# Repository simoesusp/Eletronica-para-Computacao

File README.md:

# Eletronica-para-Computacao
Material Usado na disciplina de Eletrônica para Computação

Disciplina: SSC0180 - Eletrônica para Computação

Apresentação da Disciplina

Professor: Eduardo do Valle Simões
Email: Simoes at ICMC.USP.BR
Departamento de Sistemas de Computação – ICMC - USP
Grupo de Sistemas Embarcados e Evolutivos
Laboratório de Computação Reconfigurável

Créditos Aula: 	2
Créditos Trabalho: 	2
Tipo: 	Semestral

# Projeto Alunos 2019

- TODOS OS ALUNOS PRECISAM APRESENTAR O TRABALHO PESSOALMENTE!! Incluir no seu GIT: Software; Circuito com TODAS as conexoes com o Arduino; Fotos do circuito TOP VIEW; E um video mostrando o Projeto funcionando e explicando como construiu (Upa no Youtube e poe um link no teu Github). Dai' Forca a pagina da disciplina no teu git, edita o READ.ME e Comita. Depois faz um Pull Request No git original. Veja o video:

- Disco-Sound-Beat-Led-RGB (Lucas Gabriel, Mateus Penteado, Daniel Suzumura, Frederico Bulhoes)
https://github.com/LucasGab/Led-Controller
- Sistema de desbloqueio por senha (Fernando Lincoln, Victor Kendi, Leonardo Gabriel)
https://github.com/lincolncpp/senha-controle-remoto
- [Automação Residencial (Gabriel Souza, Rafael Tavares)] (https://github.com/gsasouza/house-automation)
https://github.com/gsasouza/house-automation
- Jogo da Velha (Thiago Sena, Victor Oliveira)
https://github.com/Thiago-SDQ/jogo_da_velha
- Arduino Genius Game (Dennis Green, Pedro Cisdeli, Pedro Lourenço):
https://github.com/Haltz01/Arduino_Genius
- Automação via Bot do Telegram (Gustavo Bartholomeu Trad Souza)
https://github.com/gustavobartho/Automacao_Residencial_Telegram_Bot
- 2D Penter - Impressora 2d para plotar gráficos (Breno Cunha Queiroz, Dikson Ferreira)
https://github.com/Brenocq/2DPenter
- Bomberman (André Santana, Gabriel Ferracioli, Kevin Naoto)
https://github.com/AndreSFND/Bomberman-Arduino
- Arduino controlado por Node.js (Leonardo Antonetti, Diogo Emídio, Jorge Augusto Salgado)
https://github.com/l-a-motta/arduino-node
- Fechadura Eletrica via WebServer (Joao Pedro Berno Zanutto)
https://github.com/zanuttin/Fechadura-WebServer
- Jogo de pong (Ana Clara Amorim, Kaio Tadeu Rodrigues)
https://github.com/AnaClaraAmorim/eletronica-para-computacao
- Sensor de temperatura (Gabriel Nicolau, Daniel Froes, Guilherme, Mateus Bragança)
https://github.com/7Nic/Sensor-de-temperatura
- Robô Omnidirecional (Lucas Romera, Maria Eduarda Kawakami, Otto Fernandes)
https://github.com/ottusp/Eletronica_Arduino
- Medidor de Temperatura e Umidade (César Guibo, Leonardo Rebelo, Ricardo Nascimento)
https://github.com/Rebelo/medidor_temp_umidade
- Xiloino: um instrumento musical (Paulo José, Jonathan Sanchez, Augusto de Elet)
https://gitlab.com/ImperfectFractal/xiloino
-Leitor de Morse por luz(Anderson Cardoso, Bruna Garcia, Hellen Rosa e Mateus de Souza)
https://github.com/OhMySt4rs/LeitordeMorse
- Exibição de mensagem em matriz de leds 8x8 (Marcus Vinícius Medeiros Pará, Luca Machado Bottino)
https://github.com/MarcusMedeiros99/max7219
- Simon42-Game (Bruna Magrini, Gustavo Akira, Marlon Martins, Wellington Amaral)
https://github.com/mjmartins11/projectsimon42
- Tradutor de Codigo Morse (Luis Otavio M. Ferreira, Leonardo F. Pinheiro, Luca M. Alexander, Maria Fernanda L. de Mello)
https://github.com/LuisOtavioMF/SCC0117-Trabalho2
- Rolador de Dados, com Seleção de dados (Guilherme Hiromoto, João Victor de Araujo Lima, Murilo Franchi Paulo Matana da Rocha, Vinicius Shimizu)
https://github.com/mrlFranchi/DiceRoller
- Genius Game With Sensor (Gabriel Rossati, Nathan Rodrigues e Yure Pablo):
https://github.com/yp1plus/geniusWithSensor_game
- Piano Hero (Bruno Fernandes Moreira, Francisco Pedrosa, Savio Duarte Fontes e Thales Willian Dalvi da Silva)
https:https://github.com/FranPedrosa/PianoHero<br/>
- Arduino Robot Car (Luca Batista Barbosa e Mylena Vieira Pim)
https://github.com/mylenapim/Arduino-Robot-Car
- Tradutor para Código Morse(Daniel Vieira, Vinícius Kuhlmann, Luis Rodrigues)
https://github.com/Idalen/Arduino_Morse_Translator
- Termômetro Digital (Eduardo Souza Rocha, Fabio Dias da Cunha)<br/>
https://github.com/Edwolt/Termometro-Arduino/
- Detector de Porta Aberta (Fernando Cincinato, Olavo Morais)
https://github.com/FernandoCincinato/Detector-de-porta-aberta-Arduino
- Arduino Pong Game (Diany Pressato Larissa Freire Luana Terra do Couto Matheus Araujo Tyago Teoi)
https://github.com/M-A-rs/Arduino-Pong-Game
- Sistema de monitoramento de umidade do solo (André Vieira, Leandro Satoshi)
https://github.com/LSatoshi/Soil_Moisture_Monitoring
- Dado-inator(Bernardo Andrade,Filipe Oliveira,Victor Russo,Yasmin Araújo)
https://github.com/vrrusso/dado-inator
- Labirinto Transdimensional em primeira pessoa (Dalton Sato, Marcus Martins, Vinícius de Araújo, Vitor Amim)
https://github.com/marcuscastelo/arduino-transdimentional-maze
- Piano de Bananas (Jose Daniel, Isadora Siebert, Erick Barcelos, Pablo Oliviera)
https://github.com/pabloolvr/Piano-de-Bananas
- Osciloscópio USB (Henrique Libutti, Matheus Borella, Natan Cerdeira)
https://github.com/natanbc/stm32_usb_scope
- Medidor de Pulso (Caio Marcos Chaves Viana; Lucas Carvalho Machado; Lucas Yuiti Oda Yamamoto; Gabriel de Oliveira Guedes Nogueira; Victor Gomes de Carvalho)
https://github.com/Talendar/arduino_pulse_monitor/blob/master/README.md
- Fonte da bancada (André Niero Setti)
https://github.com/Setti7/eletronica

# Video-aulas:

Screan Captured: https://www.youtube.com/watch?v=qb6fcfDH5Qk&t=2s

Screan Captured: https://www.youtube.com/watch?v=vQig6pRj4C4

Aula Tutorial EAGLE Parte 1: https://www.youtube.com/watch?v=jCn-QlsnRMU

Aula Tutorial EAGLE Parte 2: https://www.youtube.com/watch?v=TP7zXqjaEfo

# Não Faça em Casa

 - https://www.youtube.com/watch?v=slhocFSAoQE
 - https://www.youtube.com/watch?v=jBwodg8sfdU
 - https://www.youtube.com/watch?v=jUE1IHN6OI8
 - https://www.youtube.com/watch?v=yCwmYfkTInY

# Circuitos:

Porta NOT (nMOS e CMOS) http://tinyurl.com/y5shkxya

Cadeia NOT ERRADA (NPN)! http://tinyurl.com/y2mxmgwj

Cadeia NOT ERRADA!(nMOS) http://tinyurl.com/y6le5sgn

Fonte1 (Trafo-diodos-capacitor-led) http://tinyurl.com/y5793zjk

# Objetivos:

Familiarizar os alunos com o funcionamento eletrônico das portas e lógicas com conceitos relacionados a dispositivos eletrônicos.

Programa Resumido
Conceitos básicos de circuitos eletrônicos; caracterização dos componentes básicos: resistores, capacitores, diodos e transistores; projeto de circuitos eletrônicos com componentes básicos; projeto de funções lógicas com transistores: portas lógicas digitais; simulação de sinais elétricos em circuitos eletrônicos, efeitos transitórios na propagação de sinais elétricos em circuitos de lógica digital; projetos de fontes de tensão de corrente contínua.

Programa
Conceitos básicos de circuitos eletrônicos, com ênfase na utilização de componentes eletrônicos básicos, tais como resistores, capacitores, diodos e transistores, no projeto de circuitos e portas lógicas digitais. Uso de simuladores de circuitos elétricos para visualização de formas de onda. Estudo do efeito de fontes de tensão de corrente contínua em circuitos elétricos. Aplicações de transistores como chaves binárias no projeto de funções lógicas, como portas NOT, AND, OR e XOR. Efeitos transitórios na propagação de sinais elétricos em circuitos de lógica digital, como tempos de subida e descida, efeitos fan-out e suas formas de ondas. Circuitos NMOS e CMOS: caracterização e efeitos de variação de voltagem e frequência.

Avaliação
     	Método
     	Exposição seguida de exercícios e trabalhos práticos, dentro e fora de classe.

     	Critério
     	Teremos dois trabalhos T1 e T2 e a nota final será a média aritmética entre eles: NF = (T1 + T2 )/2,
      sendo que é necessário obter nota superior a CINCO em ambos os trabalhos.

     	Norma de Recuperação
     	Critério de Aprovação:
      NP+(Mrec/2,5), se Mrec >= 7,5; ou Max {NP,Mrec}, se Mrec <= 5,0;
      ou 5,0, se 5,0 <= Mrec < 7,5.( NP=1ª avaliação, Mrec=prova recuperação).

Bibliografia
Livro-texto:
- ANNIBAL, HETTEM JR, Fundamentos de Informática – Eletrônica para Computação.

Bibliografia complementar:
- SEDRA, SMITH, Microeletrônica, Makron Books, 2000.

1) Brophy, James John: Eletronica basica.
 Rio de Janeiro Guanabara Dois 1978.
Biblioteca:  68M05.10 B869e e.1

Sequência da Disciplina:

SSC-180 Eletrônica Para Computação

SSC-117 – Introdução à Lógica Digital I

SSC-118 Sistemas Digitais

SSC-112 - Organização de Computadores Digitais I
(SSC-119 – Prática em Organização de Computadores)

SSC-114 - Arquitetura de Computadores,

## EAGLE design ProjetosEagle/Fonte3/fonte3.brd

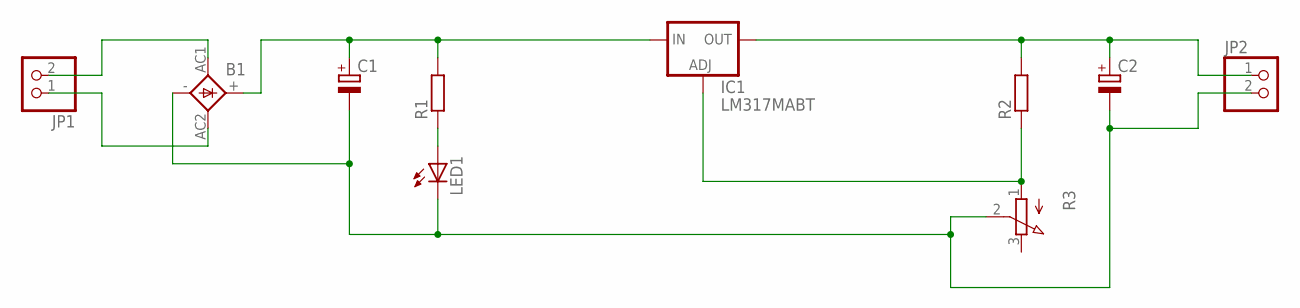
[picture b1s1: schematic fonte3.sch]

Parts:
B1: 1KAB
C1, C2: CPOL-EUE5-10.5; E5-10,5
IC1: LM317MABT; TO220L1
JP1, JP2: PINHD-1X2; 1X02
LED1: LED5MM
R1, R2: R0207/10; 0207/10
R3: 3RP/1610N

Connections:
unnamed: B1.AC1, JP1.2
unnamed: B1.AC2, JP1.1
unnamed: B1.+, C1.+, IC1.3 (IN), R1.2
unnamed: LED1.A, R1.1
unnamed: C2.+, IC1.2 (OUT), JP2.1, R2.2
unnamed: IC1.1 (ADJ), R2.1, R3.1 (A)
unnamed: B1.-, C1.-, C2.-, JP2.2, LED1.K (C), R3.2 (S)

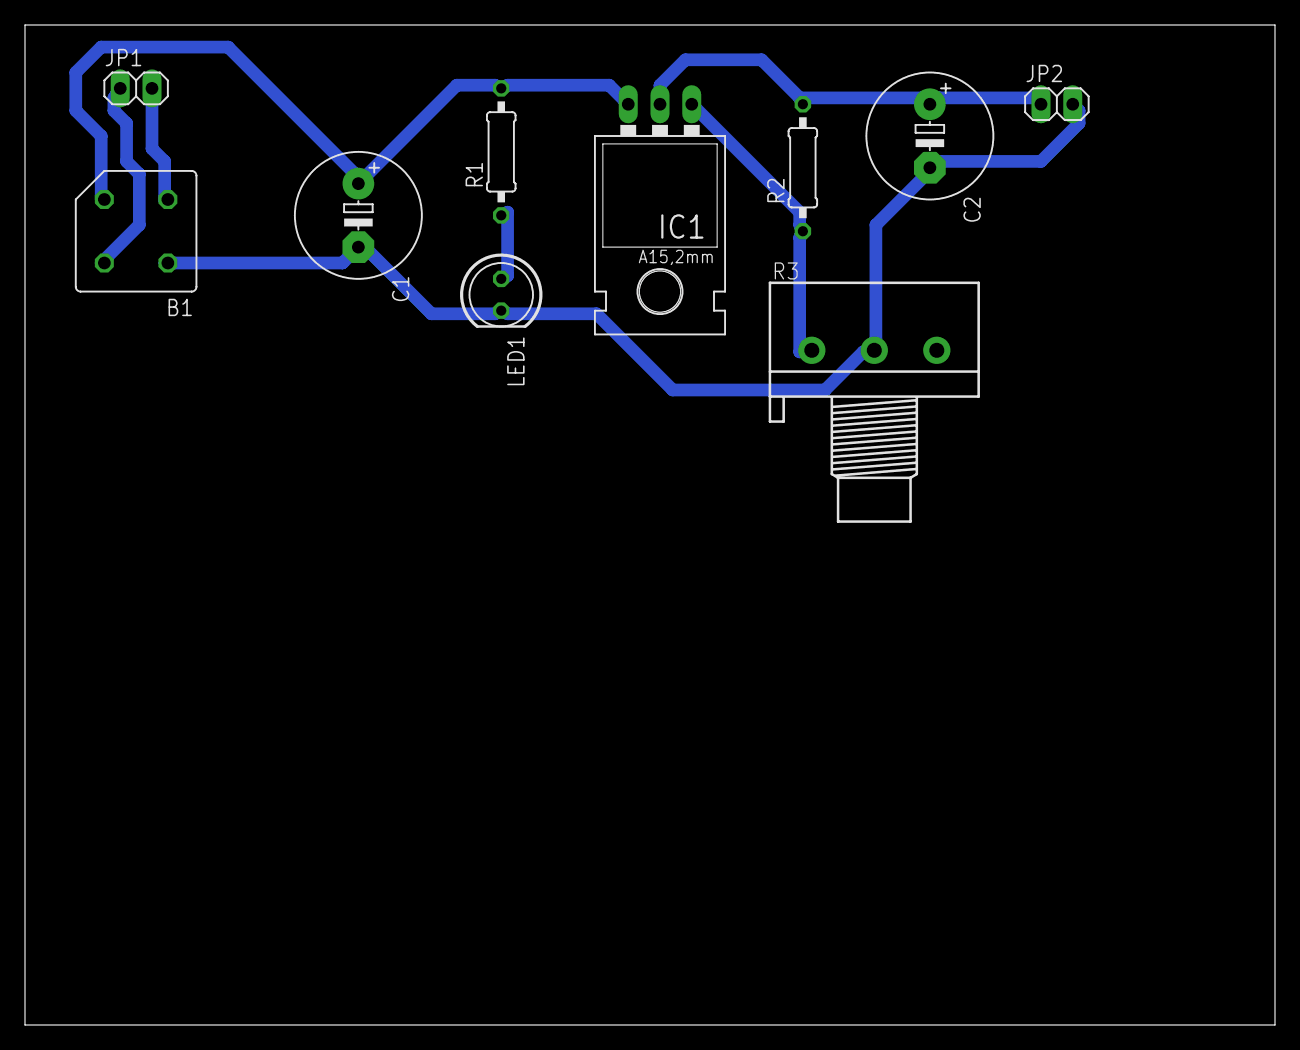
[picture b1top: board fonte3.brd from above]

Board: 2 copper layers, 100.0 x 80.0 mm, 10 parts (0 on the bottom side), 7 nets.

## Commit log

2017-05-02 Add arduino project
    Robot + Sonar + BT Remote Control
    Android APK = BT Remote control
2018-06-06 add_SpiceandAulas
2018-06-08 readme
2019-06-18 Update README.md
    Adicionado Projeto aluno turma A
2019-06-18 Update README.md
    Adicionado projeto (turma A)
2019-06-25 add project "automação residencial"
2019-06-27 Update README.md
    Adicionado projeto
2019-06-27 Update README.md
    Adicionando link para o projeto Arduino Genius, feito por Dennis Green, Pedro Cisdeli, Pedro Lourenço.
2019-06-28 Update README.md
    Adicionei o meu projeto à lista de projetos
2019-06-28 Update README.md
    Adicionei o link do repositório do meu projeto à lista de projetos
2019-06-28 Update README.md
    Adicionei o link do meu projeto à lista
2019-06-28 Update README.md
    Adicionado o projeto do Rolador de dados
2019-06-29 Update README.md
    Added Transdimentional Maze
2019-06-29 Update README.md
    Adcionando meu projeto.
2019-06-29 Update README.md
    Inclusão do projeto do detector de porta aberta
    Grupo: Fernando Cincinato e Olavo Morais
2019-07-01 Adição de um projeto
2019-07-01 Update README.md
    Adicionamos o projeto Arduino Robot Car
2019-07-01 Update README.md
    Adicionado projeto Piano Hero
2019-07-01 Inserção do Projeto Genius com Sensor
2019-07-01 Update README.md
    inclusão do projeto simon42-game
2019-07-02 Repositório do Xiloino adicionado ao README
2019-07-03 Update README.md
    Adicionei meu projeto
2019-07-03 Adicionando Projeto de 2019
    Adicionando o projeto: Sensor de temperatura (Gabriel Nicolau, Daniel Froes, Guilherme, Mateus Bragança)
2019-07-04 Adicionado projeto de fechadura eletronica por webserver
2019-07-07 Update README.md
    Adicionado grupo do bomberman
2019-08-09 Adicionado projeto 2D Penter
